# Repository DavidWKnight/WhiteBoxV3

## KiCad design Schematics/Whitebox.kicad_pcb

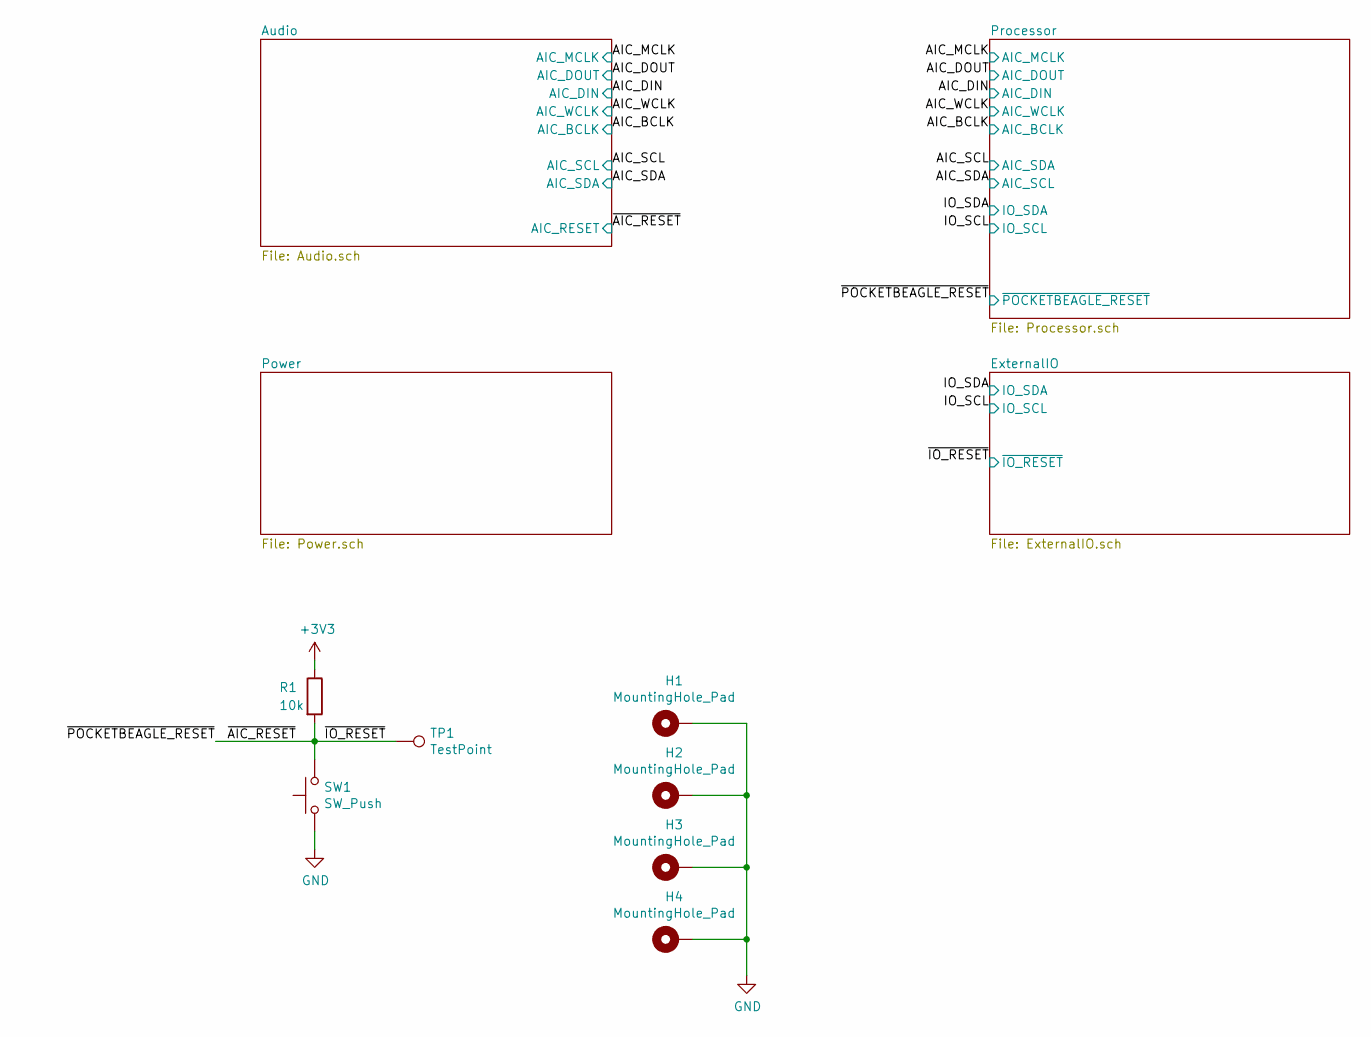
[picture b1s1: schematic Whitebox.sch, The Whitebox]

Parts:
H1, H2, H3, H4: MountingHole_Pad; MountingHole_2.2mm_M2_Pad
R1: 10k; R_0805_2012Metric; LCSC Part # C17414
SW1: SW_Push; SW_PUSH_6mm
TP1: TestPoint; TestPoint_Keystone_5010-5014_Multipurpose

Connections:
+3V3: R1.1; also elsewhere on the board
/~AIC_RESET: R1.2, SW1.2, TP1.1; also elsewhere on the board

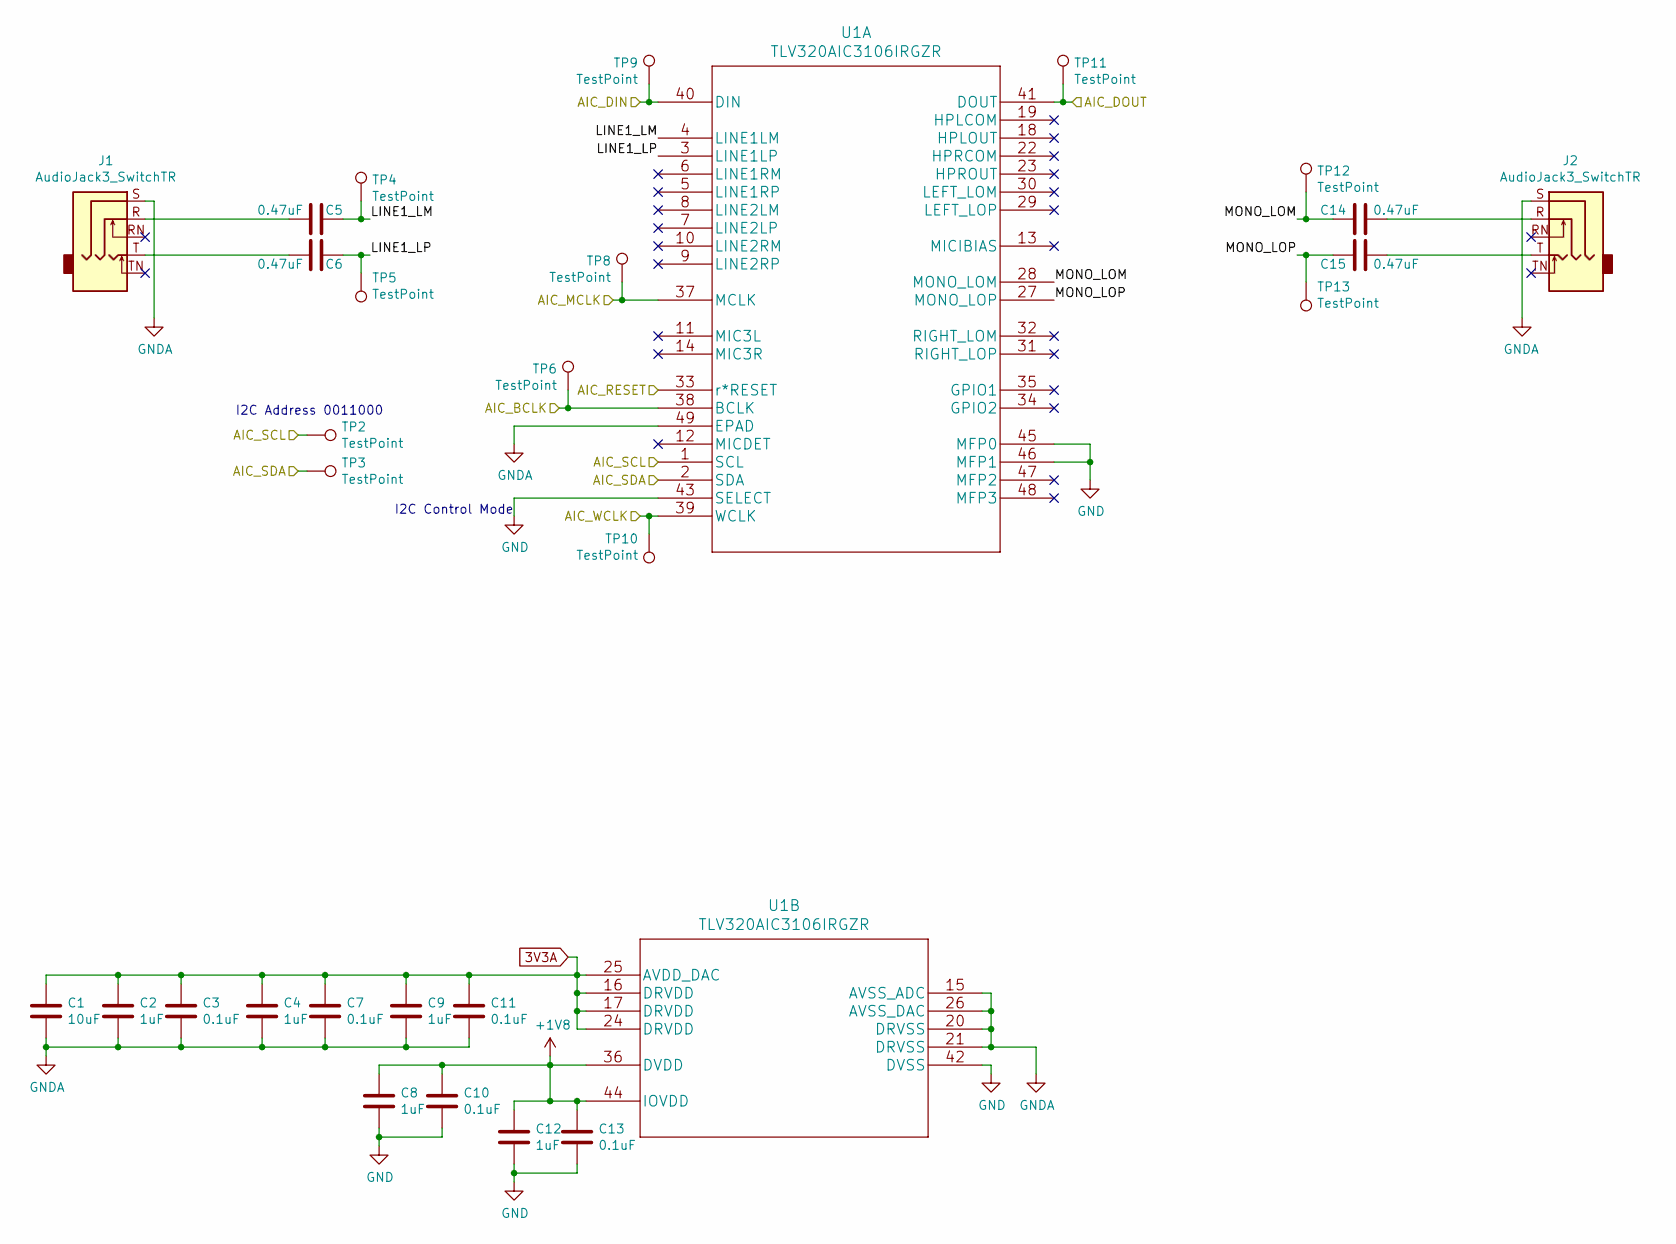
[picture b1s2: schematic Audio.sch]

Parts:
C1: 10uF; C_0805_2012Metric; LCSC Part # C15850
C2, C4, C8, C9, C12: 1uF; C_0805_2012Metric; LCSC Part # C28323
C3, C7, C10, C11, C13: 0.1uF; C_0805_2012Metric; LCSC Part # C28233
C5, C6, C14, C15: 0.47uF; C_0805_2012Metric; LCSC Part # C13967
J1, J2: AudioJack3_SwitchTR; SN37A14B
TP2, TP3, TP4, TP5, TP6, TP8, TP9, TP10, TP11, TP12, TP13: TestPoint; TestPoint_Keystone_5010-5014_Multipurpose
U1: TLV320AIC3106IRGZR; VQFN-48-1EP_7x7mm_P0.5mm_EP5.15x5.15mm; LCSC Part # C183086

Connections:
3V3A: C1.2, C2.2, C3.2, C4.2, C7.2, C9.2, C11.2, U1.16 (DRVDD), U1.17 (DRVDD), U1.24 (DRVDD), U1.25 (AVDD_DAC); also elsewhere on the board
+1V8: C8.2, C10.2, C12.2, C13.2, U1.36 (DVDD), U1.44 (IOVDD); also elsewhere on the board
/AIC_BCLK: TP6.1, U1.38 (BCLK); also elsewhere on the board
/AIC_DIN: TP9.1, U1.40 (DIN); also elsewhere on the board
/AIC_DOUT: TP11.1, U1.41 (DOUT); also elsewhere on the board
/AIC_MCLK: TP8.1, U1.37 (MCLK); also elsewhere on the board
/AIC_SCL: TP2.1, U1.1 (SCL); also elsewhere on the board
/AIC_SDA: TP3.1, U1.2 (SDA); also elsewhere on the board
/AIC_WCLK: TP10.1, U1.39 (WCLK); also elsewhere on the board
/Audio/LINE1_LM: C5.2, TP4.1, U1.4 (LINE1LM)
/Audio/LINE1_LP: C6.2, TP5.1, U1.3 (LINE1LP)
/Audio/MONO_LOM: C14.2, TP12.1, U1.28 (MONO_LOM)
/Audio/MONO_LOP: C15.2, TP13.1, U1.27 (MONO_LOP)
/~AIC_RESET: U1.33 (r*RESET); also elsewhere on the board
unnamed: C5.1, J1.R
unnamed: C6.1, J1.T
unnamed: C14.1, J2.R
unnamed: C15.1, J2.T

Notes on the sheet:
I2C Control Mode
I2C Address 0011000

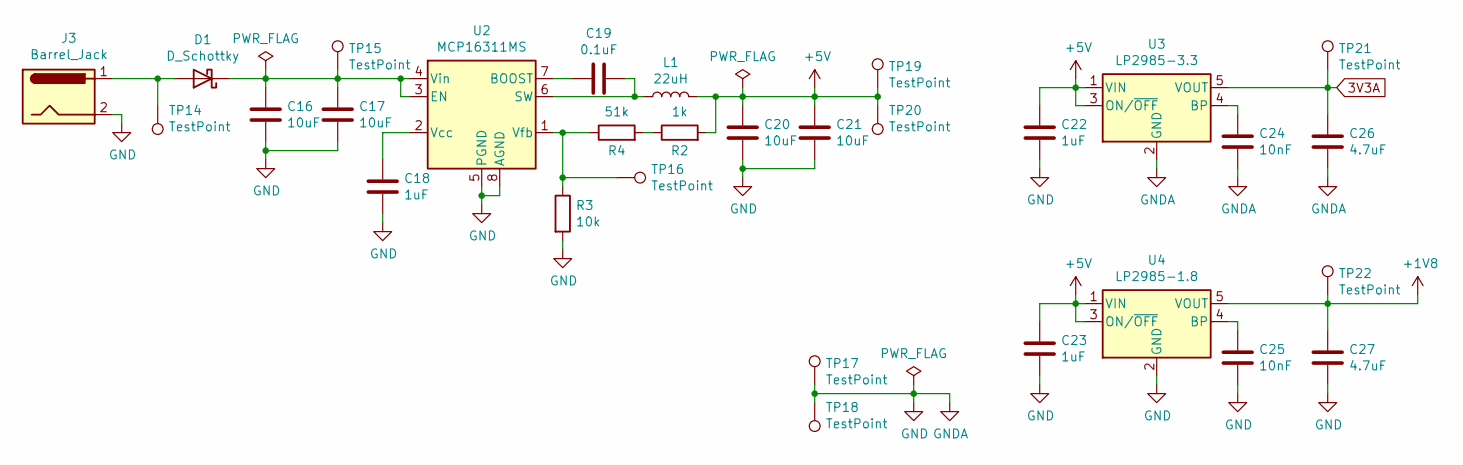
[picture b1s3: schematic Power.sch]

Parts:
C16, C17, C20, C21: 10uF; C_0805_2012Metric; LCSC Part # C15850
C18, C22, C23: 1uF; C_0805_2012Metric; LCSC Part # C28323
C19: 0.1uF; C_0805_2012Metric; LCSC Part # C28233
C24, C25: 10nF; C_0805_2012Metric; LCSC Part # C1710
C26, C27: 4.7uF; C_0805_2012Metric; LCSC Part # C1779
D1: D_Schottky; D_SMA; LCSC Part # C24784
J3: Barrel_Jack; BarrelJack_CUI_PJ-063AH_Horizontal
L1: 22uH; L_Vishay_IHLP-2020
R2: 1k; R_0805_2012Metric; LCSC Part # C17513
R3: 10k; R_0805_2012Metric; LCSC Part # C17414
R4: 51k; R_0805_2012Metric; LCSC Part # C17737
TP14, TP15, TP16, TP17, TP18, TP19, TP20, TP21, TP22: TestPoint; TestPoint_Keystone_5010-5014_Multipurpose
U2: MCP16311MS; MSOP-8_3x3mm_P0.65mm; LCSC Part # C107454
U3: LP2985-3.3; SOT-23-5; LCSC Part # C89826
U4: LP2985-1.8; SOT-23-5; LCSC Part # C95415

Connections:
3V3A: C26.1, TP21.1, U3.5 (VOUT); also elsewhere on the board
+1V8: C27.1, TP22.1, U4.5 (VOUT); also elsewhere on the board
unnamed: C16.1, C17.1, D1.1 (K), TP15.1, U2.3 (EN), U2.4 (Vin)
unnamed: C18.1, U2.2 (Vcc)
unnamed: C19.1, L1.1, U2.6 (SW)
unnamed: C19.2, U2.7 (BOOST)
unnamed: C24.1, U3.4 (BP)
unnamed: C25.1, U4.4 (BP)
unnamed: D1.2 (A), J3.1, TP14.1
unnamed: R2.1, R4.2
unnamed: R3.1, R4.1, TP16.1, U2.1 (Vfb)

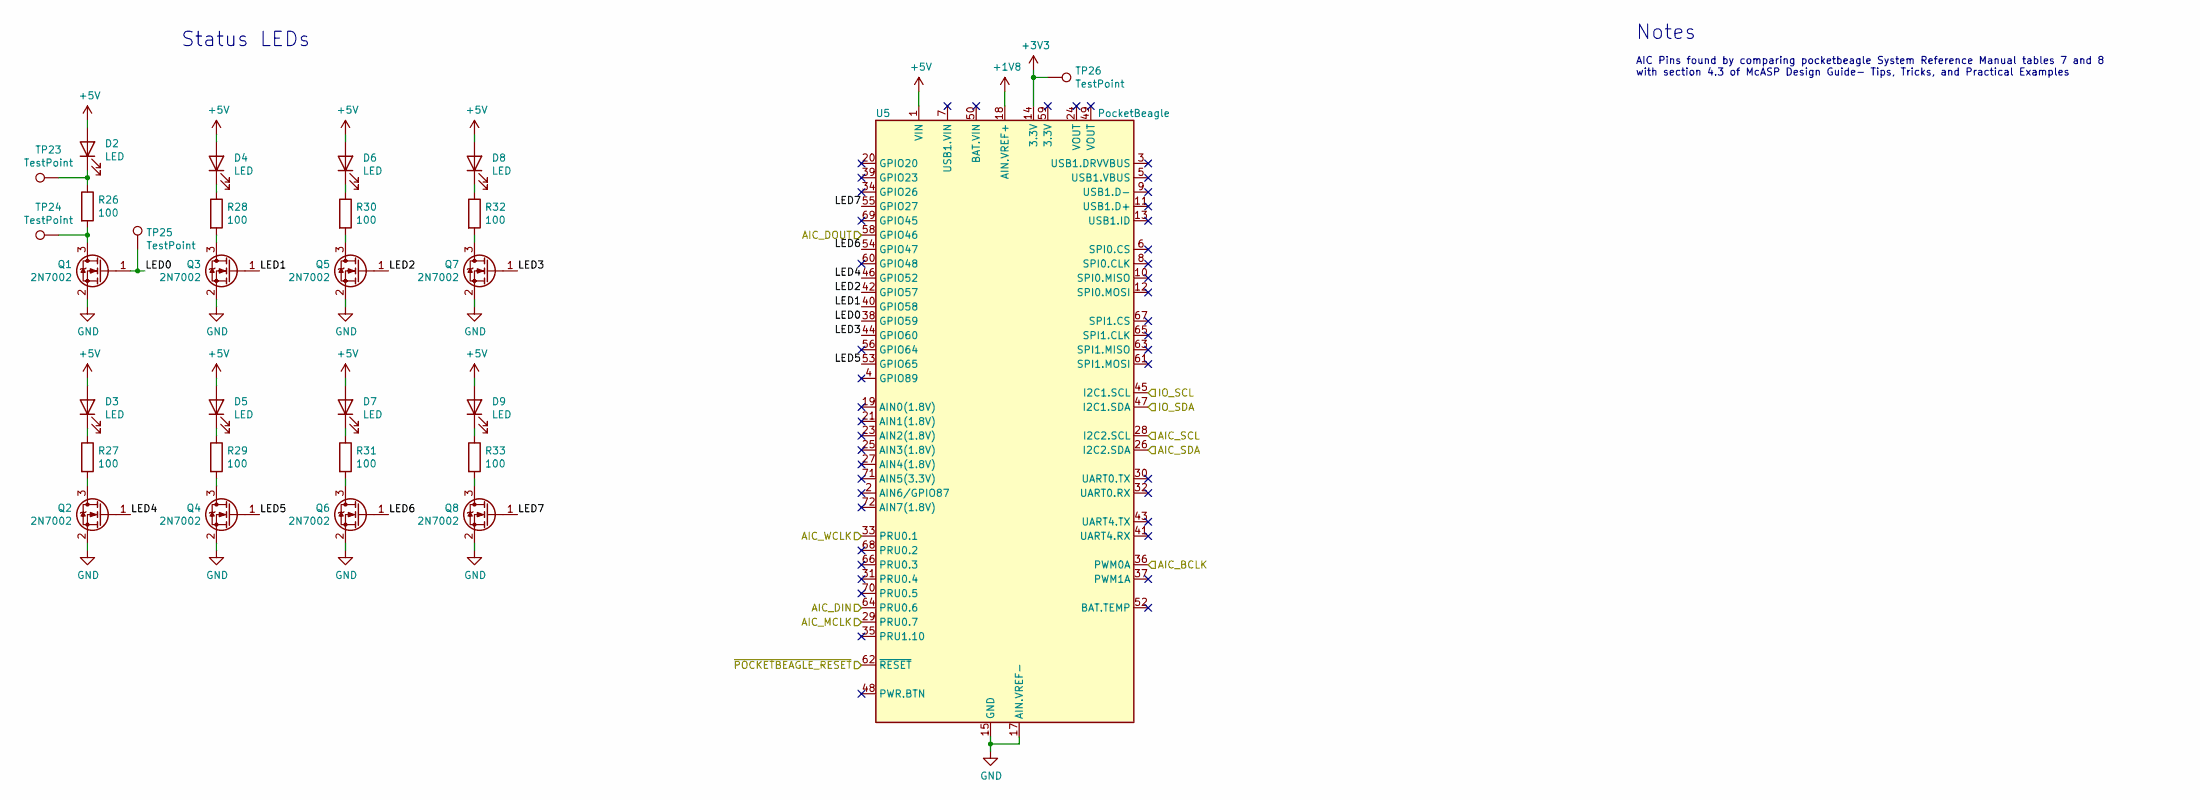
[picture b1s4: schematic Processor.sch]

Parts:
D2, D3, D4, D5, D6, D7, D8, D9: LED; D_0603_1608Metric; LCSC Part # C72041
Q1, Q2, Q3, Q4, Q5, Q6, Q7, Q8: 2N7002; SOT-23; LCSC Part # C8545
R26, R27, R28, R29, R30, R31, R32, R33: 100; R_0805_2012Metric; LCSC Part # C17408
TP23, TP24, TP25, TP26: TestPoint; TestPoint_Keystone_5010-5014_Multipurpose
U5: PocketBeagle; BeagleBoard_PocketBeagle

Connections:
+1V8: U5.18 (AIN.VREF+); also elsewhere on the board
+3V3: TP26.1, U5.14 (3.3V); also elsewhere on the board
/AIC_BCLK: U5.36 (PWM0A); also elsewhere on the board
/AIC_DIN: U5.64 (PRU0.6); also elsewhere on the board
/AIC_DOUT: U5.58 (GPIO46); also elsewhere on the board
/AIC_MCLK: U5.29 (PRU0.7); also elsewhere on the board
/AIC_SCL: U5.26 (I2C2.SDA); also elsewhere on the board
/AIC_SDA: U5.28 (I2C2.SCL); also elsewhere on the board
/AIC_WCLK: U5.33 (PRU0.1); also elsewhere on the board
/IO_SCL: U5.45 (I2C1.SCL); also elsewhere on the board
/IO_SDA: U5.47 (I2C1.SDA); also elsewhere on the board
/Processor/LED0: Q1.1 (G), TP25.1, U5.38 (GPIO59)
/Processor/LED1: Q3.1 (G), U5.40 (GPIO58)
/Processor/LED2: Q5.1 (G), U5.42 (GPIO57)
/Processor/LED3: Q7.1 (G), U5.44 (GPIO60)
/Processor/LED4: Q2.1 (G), U5.46 (GPIO52)
/Processor/LED5: Q4.1 (G), U5.53 (GPIO65)
/Processor/LED6: Q6.1 (G), U5.54 (GPIO47)
/Processor/LED7: Q8.1 (G), U5.55 (GPIO27)
/~AIC_RESET: U5.62 (~RESET); also elsewhere on the board
unnamed: D2.1 (K), R26.1, TP23.1
unnamed: D3.1 (K), R27.1
unnamed: D4.1 (K), R28.1
unnamed: D5.1 (K), R29.1
unnamed: D6.1 (K), R30.1
unnamed: D7.1 (K), R31.1
unnamed: D8.1 (K), R32.1
unnamed: D9.1 (K), R33.1
unnamed: Q1.3 (D), R26.2, TP24.1
unnamed: Q2.3 (D), R27.2
unnamed: Q3.3 (D), R28.2
unnamed: Q4.3 (D), R29.2
unnamed: Q5.3 (D), R30.2
unnamed: Q6.3 (D), R31.2
unnamed: Q7.3 (D), R32.2
unnamed: Q8.3 (D), R33.2

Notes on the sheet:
AIC Pins found by comparing pocketbeagle System Reference Manual tables 7 and 8 with section 4.3 of McASP Design Guide- Tips, Tricks, and Practical Examples
Notes
Status LEDs

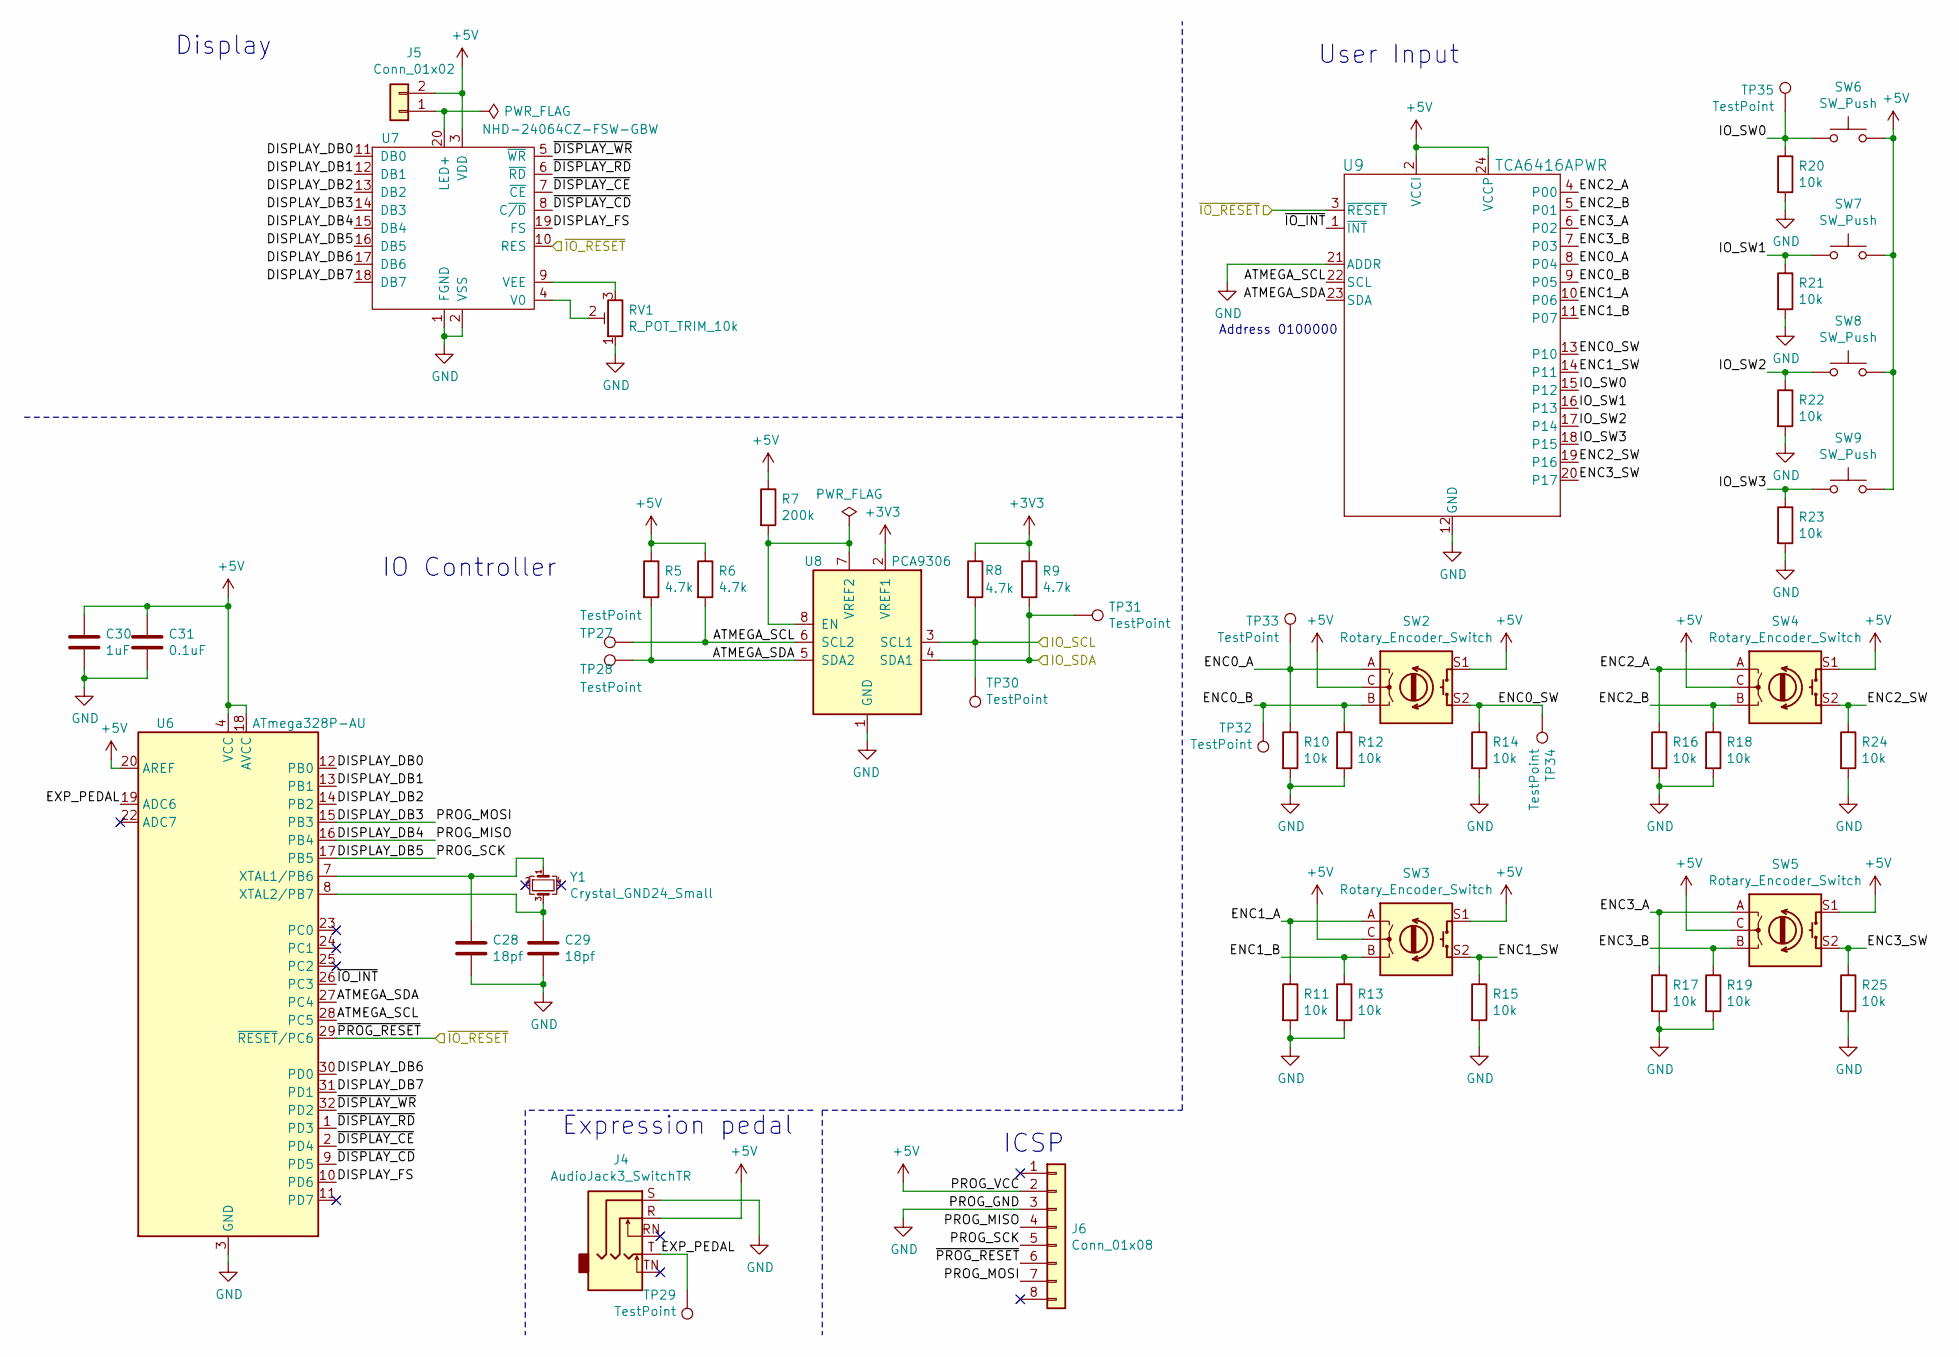
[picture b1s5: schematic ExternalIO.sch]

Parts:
C28, C29: 18pf; C_0603_1608Metric; LCSC Part # C1647
C30: 1uF; C_0805_2012Metric; LCSC Part # C28323
C31: 0.1uF; C_0805_2012Metric; LCSC Part # C28233
J4: AudioJack3_SwitchTR; SN37A14B
J5: Conn_01x02; PinHeader_1x02_P2.54mm_Vertical
J6: Conn_01x08; PinHeader_1x08_P2.54mm_Vertical
R5, R6, R8, R9: 4.7k; R_0805_2012Metric; LCSC Part # C17673
R7: 200k; R_0805_2012Metric; LCSC Part # C17539
R10, R11, R12, R13, R14, R15, R16, R17, R18, R19, R20, R21, R22, R23, R24, R25: 10k; R_0805_2012Metric; LCSC Part # C17414
RV1: R_POT_TRIM_10k; Potentiometer_Bourns_3296Z_Horizontal
SW2, SW3, SW4, SW5: Rotary_Encoder_Switch; RotaryEncoder_Alps_EC11E-Switch_Vertical_H20mm
SW6, SW7, SW8, SW9: SW_Push; SW_PUSH_6mm
TP27, TP28, TP29, TP30, TP31, TP32, TP33, TP34, TP35: TestPoint; TestPoint_Keystone_5010-5014_Multipurpose
U6: ATmega328P-AU; TQFP-32_7x7mm_P0.8mm; LCSC Part # C14877
U7: NHD-24064CZ-FSW-GBW
U8: PCA9306; VSSOP-8_2.3x2mm_P0.5mm; LCSC Part # C33196
U9: TCA6416APWR; TSSOP-24_4.4x7.8mm_P0.65mm; LCSC Part # C130203
Y1: Crystal_GND24_Small; Crystal_SMD_Abracon_ABM8G-4Pin_3.2x2.5mm; LCSC Part # C179641

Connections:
+3V3: R8.1, R9.1, U8.2 (VREF1); also elsewhere on the board
/ExternalIO/ATMEGA_SCL: R6.2, TP27.1, U6.28 (PC5), U8.6 (SCL2), U9.22 (SCL)
/ExternalIO/ATMEGA_SDA: R5.2, TP28.1, U6.27 (PC4), U8.5 (SDA2), U9.23 (SDA)
/ExternalIO/DISPLAY_DB0: U6.12 (PB0), U7.11 (DB0)
/ExternalIO/DISPLAY_DB1: U6.13 (PB1), U7.12 (DB1)
/ExternalIO/DISPLAY_DB2: U6.14 (PB2), U7.13 (DB2)
/ExternalIO/DISPLAY_DB3: J6.7, U6.15 (PB3), U7.14 (DB3)
/ExternalIO/DISPLAY_DB4: J6.4, U6.16 (PB4), U7.15 (DB4)
/ExternalIO/DISPLAY_DB5: J6.5, U6.17 (PB5), U7.16 (DB5)
/ExternalIO/DISPLAY_DB6: U6.30 (PD0), U7.17 (DB6)
/ExternalIO/DISPLAY_DB7: U6.31 (PD1), U7.18 (DB7)
/ExternalIO/DISPLAY_FS: U6.10 (PD6), U7.19 (FS)
/ExternalIO/ENC0_A: R10.1, SW2.A, TP33.1, U9.8 (P04)
/ExternalIO/ENC0_B: R12.1, SW2.B, TP32.1, U9.9 (P05)
/ExternalIO/ENC0_SW: R14.1, SW2.S2, TP34.1, U9.13 (P10)
/ExternalIO/ENC1_A: R11.1, SW3.A, U9.10 (P06)
/ExternalIO/ENC1_B: R13.1, SW3.B, U9.11 (P07)
/ExternalIO/ENC1_SW: R15.1, SW3.S2, U9.14 (P11)
/ExternalIO/ENC2_A: R16.1, SW4.A, U9.4 (P00)
/ExternalIO/ENC2_B: R18.1, SW4.B, U9.5 (P01)
/ExternalIO/ENC2_SW: R24.1, SW4.S2, U9.19 (P16)
/ExternalIO/ENC3_A: R17.1, SW5.A, U9.6 (P02)
/ExternalIO/ENC3_B: R19.1, SW5.B, U9.7 (P03)
/ExternalIO/ENC3_SW: R25.1, SW5.S2, U9.20 (P17)
/ExternalIO/EXP_PEDAL: J4.T, TP29.1, U6.19 (ADC6)
/ExternalIO/IO_SW0: R20.1, SW6.1, TP35.1, U9.15 (P12)
/ExternalIO/IO_SW1: R21.1, SW7.1, U9.16 (P13)
/ExternalIO/IO_SW2: R22.1, SW8.1, U9.17 (P14)
/ExternalIO/IO_SW3: R23.1, SW9.1, U9.18 (P15)
/ExternalIO/~DISPLAY_CD: U6.9 (PD5), U7.8 (C~/D)
/ExternalIO/~DISPLAY_CE: U6.2 (PD4), U7.7 (~CE)
/ExternalIO/~DISPLAY_RD: U6.1 (PD3), U7.6 (~RD)
/ExternalIO/~DISPLAY_WR: U6.32 (PD2), U7.5 (~WR)
/ExternalIO/~IO_INT: U6.26 (PC3), U9.1 (~INT)
/IO_SCL: R8.2, TP30.1, U8.3 (SCL1); also elsewhere on the board
/IO_SDA: R9.2, TP31.1, U8.4 (SDA1); also elsewhere on the board
/~AIC_RESET: J6.6, U6.29 (~RESET~/PC6), U7.10 (RES), U9.3 (~RESET); also elsewhere on the board
unnamed: C28.1, U6.7 (XTAL1/PB6), Y1.1
unnamed: C29.1, U6.8 (XTAL2/PB7), Y1.3
unnamed: J5.1, U7.20 (LED+)
unnamed: R7.2, U8.7 (VREF2), U8.8 (EN)
unnamed: RV1.2, U7.4 (V0)
unnamed: RV1.3, U7.9 (VEE)

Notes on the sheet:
Display
Address 0100000
User Input
ICSP
Expression pedal
IO Controller

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
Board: 4 copper layers, 148 parts (126 on the bottom side), 97 nets, no tracks yet.

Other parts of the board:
J7: Conn_01x02; PinHeader_1x02_P2.54mm_Vertical
P1: star_ground

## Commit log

2020-06-17 Created schematic
2020-06-17 Created gitignore and removed ignored files
2020-06-17 Renamed schematics folder and unignored kicad lib files
2020-06-18 Finished initial component placement
